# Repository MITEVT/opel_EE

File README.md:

# opel_EE

A collection of repositories relating to our Electric Opel GT Project

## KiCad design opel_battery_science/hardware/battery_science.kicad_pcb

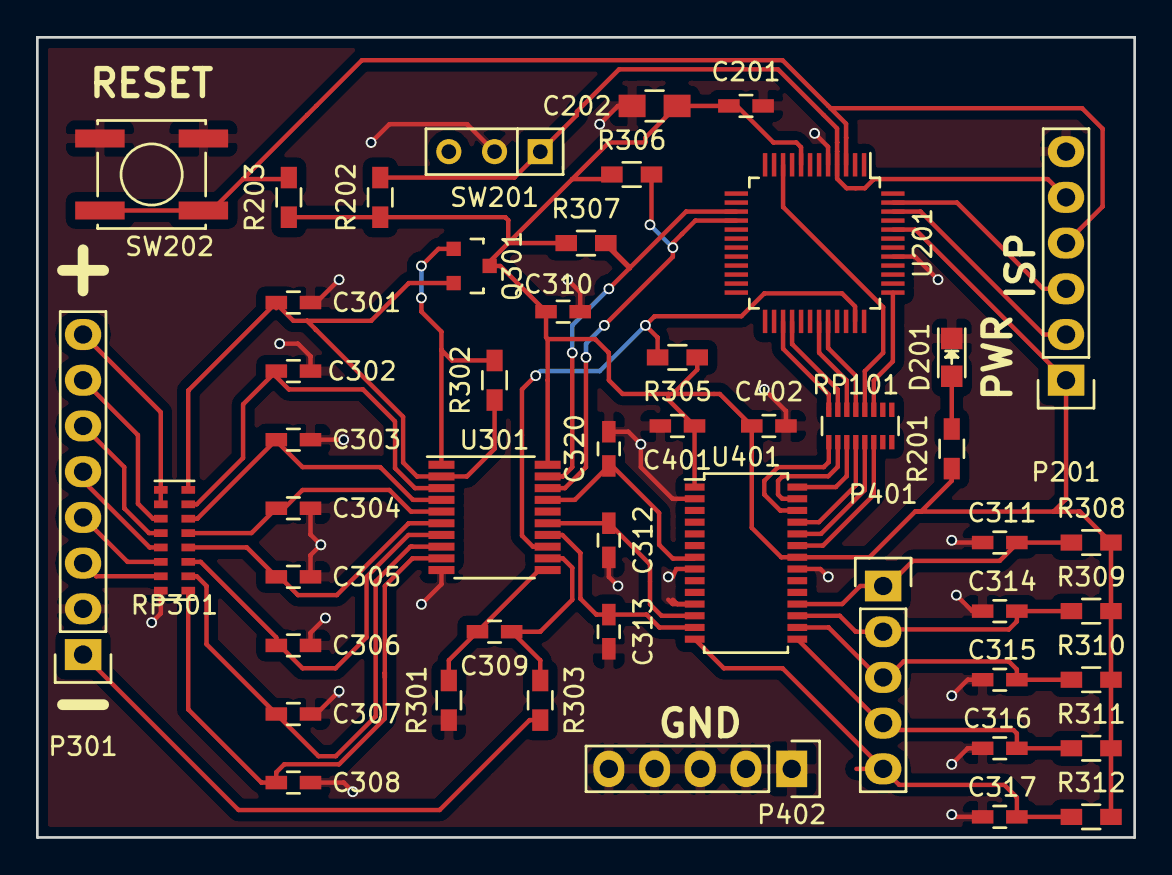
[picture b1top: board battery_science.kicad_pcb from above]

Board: 2 copper layers, 61.0 x 44.5 mm, 49 parts (0 on the bottom side), 48 nets.

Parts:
C201, C309, C311, C312, C314, C315, C316, C317: .1μF; C_0603_HandSoldering
C202: 1μF; C_0805_HandSoldering
C301: 10μF; C_0603_HandSoldering
C302, C303, C304, C305, C306, C307, C308, C320: 1μF; C_0603_HandSoldering
C310: 4.7μF; C_0603_HandSoldering
C313: 1nF; C_0603_HandSoldering
C401, C402: 100nF; C_0603_HandSoldering
D201: LED; LED_0805
P201: CONN_01X06; Pin_Header_Straight_1x06
P301: CONN_01X08; Pin_Header_Straight_1x08
P401, P402: CONN_01X05; Pin_Header_Straight_1x05
Q301: BSS84; SOT-23
R201: 100; R_0603_HandSoldering
R202, R203, R308, R309, R310, R311, R312: 10k; R_0603_HandSoldering
R301, R303: 1k; R_0603_HandSoldering
R302: 200k; R_0603_HandSoldering
R305, R306, R307: 4.7k; R_0603_HandSoldering
RP101: 47Ω; R_Array_Convex_8x0602
RP301: CAY16-101J8LF; R_Cat16-8
SW201: SPST; SW_Micro_SPST
SW202: SPST; SW_SPST_EVPBF
U201: LPC11C14; LQFP-48_7x7mm_Pitch0.5mm
U301: BQ76925; TSSOP-20_4.4x6.5mm_Pitch0.65mm
U401: ADS1148IPWR; TSSOP-28_4.4x9.7mm_Pitch0.65mm

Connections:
+3V3: C201.1, C202.1, C310.1, C401.1, C402.1, P201.1, Q301.3, R201.1, R202.1, R203.1, R305.1, R306.1, R307.1, R308.2, R309.2, R310.2, R311.2, R312.2, U201.8, U201.44, U301.20, U401.1, U401.22
/ADC/Thermistors/CS: RP101.5, U401.24
/ADC/Thermistors/DIN: RP101.2, U401.27
/ADC/Thermistors/DOUT: RP101.1, U401.26
/ADC/Thermistors/DRDY: RP101.4, U401.25
/ADC/Thermistors/SCLK: RP101.3, U401.28
/ADC/Thermistors/START: RP101.6, U401.23
/ADC/Thermistors/TH1: C311.1, P401.1, R308.1, U401.18
/ADC/Thermistors/TH2: C314.1, P401.2, R309.1, U401.17
/ADC/Thermistors/TH3: C315.1, P401.3, R310.1, U401.16
/ADC/Thermistors/TH4: C316.1, P401.4, R311.1, U401.15
/ADC/Thermistors/TH5: C317.1, P401.5, R312.1, U401.14
/ADC/Thermistors/VCOUT: C312.1, U301.15, U401.12
/ADC/Thermistors/VIOUT: C313.1, U301.14, U401.13
/ADC/Thermistors/VREF: C320.1, U301.17, U401.7
/BatteryMonitoring/ALERT: R305.2, U201.35, U301.13
/BatteryMonitoring/SCL: R307.2, U201.15, U301.19
/BatteryMonitoring/SDA: R306.2, U201.16, U301.18
/microcontroller/DRDY: RP101.13, U201.32
/microcontroller/MISO: RP101.16, U201.27
/microcontroller/MOSI: RP101.15, U201.28
/microcontroller/PROGRAM: P201.5, R202.2, SW201.1, U201.4
/microcontroller/RESET: P201.4, R203.2, SW202.1, U201.3
/microcontroller/RXD: P201.2, U201.46
/microcontroller/SCK: RP101.14, U201.31
/microcontroller/SSEL: RP101.12, U201.10
/microcontroller/START: RP101.11, U201.37
/microcontroller/TXD: P201.3, U201.47
GND: C201.2, C202.2, C301.2, C302.2, C303.2, C304.2, C305.2, C306.2, C307.2, C308.2, C310.2, C311.2, C312.2, C313.2, C314.2, C315.2, C316.2, C317.2, C320.2, C401.2, C402.2, D201.1, P201.6, P301.2, P402.1, P402.2, P402.3, P402.4, P402.5, R301.2, RP301.8, SW201.2, SW202.2, U201.5, U201.41, U301.10, U401.2, U401.8, U401.11, U401.21
unnamed: C301.1, Q301.2, R302.1, RP301.16, U301.2
unnamed: C302.1, RP301.15, U301.3
unnamed: C303.1, RP301.14, U301.4
unnamed: C304.1, RP301.13, U301.5
unnamed: C305.1, RP301.12, U301.6
unnamed: C306.1, RP301.11, U301.7
unnamed: C307.1, RP301.10, U301.8
unnamed: C308.1, RP301.9, U301.9
unnamed: C309.1, R303.1, U301.12
unnamed: C309.2, R301.1, U301.11
unnamed: D201.2, R201.2
unnamed: P301.1, R303.2
unnamed: P301.3, RP301.7
unnamed: P301.4, RP301.6
unnamed: P301.5, RP301.5
unnamed: P301.6, RP301.4
unnamed: P301.7, RP301.3
unnamed: P301.8, RP301.1, RP301.2
unnamed: Q301.1, R302.2, U301.1

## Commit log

2015-09-19 Initial Repo Setup
2015-09-19 Added KICAD libraries
2015-10-03 tete
2015-10-03 blah
2015-10-03 asldjf
2015-10-03 The log for the MiniMon
2015-10-03 Minimon screenshot
2015-10-10 finish
2015-10-10 Added dev board sub module
2015-10-10 fixing repo
2015-10-10 more fixing
2015-10-10 adding spec
2015-10-10 Updated spec
2015-10-10 Removed bullshit"
2015-10-10 This is a commit I'm doing
    This is a more detailed explanation of the the commit because hell yeah
2015-10-10 adding initial python validator
2015-10-10 updated can spec
2015-10-11 finished spec validator and format
2015-10-12 progress on log analysis
2015-10-12 removing swp files
2015-10-13 finish validator
2015-10-13 remove debug print
2015-10-14 fix bug involving error reporting and boundary checking
2015-10-16 cleanup of repo
2015-10-16 complete dev board schematic and layout
2015-10-17 remove can_validator from here.
2015-10-17 add can_validator submodule
2015-10-17 remove can_validator again
2015-10-24 Fixed many example errors
2015-10-24 Created template and added unionized data structure in CAN message object
2015-10-30 Added unit tests to tempalte and resolved soem compiler warnings
2015-11-14 Added PDM
2015-11-14 added opel fusebox
2015-11-21 Finished final template outeline
2015-11-21 Added 12V
2016-01-09 Velocity sensor circuit added
2016-01-16 hardware: initial commit
2016-04-02 relay box schematics first commit
2016-04-09 relay box updates
2016-04-09 updates to relay box schematics
2016-04-23 relay schematic updates and relay library
2016-04-30 updated relay box schematics, added VCF4-1000 footprint
2016-06-17 Created fake DI
2016-07-01 TestDI added UART printing
2016-07-12 Some changes, commiting before I mess with computer
2016-07-28 Added battery science code
2016-07-29 Fixed negative numbers
2016-07-29 Fixed errors and warnings
2016-07-31 Added new features, never had a successful test of measuring voltages with resistors
2016-08-05 Added PCB design
2016-08-08 Changes to offset and gain correction
2016-08-08 Fixed readings
2016-08-09 Added external ADC, fixed power
2016-08-09 Swapped out ADC part number
2016-08-15 Many fixes, corrected schematic, roughly tried to partition board
2016-08-16 Added ground connection for differnetial input
2016-08-16 Moved input pins for ease of programming and avoiding accidental negative readings
2016-09-17 Changes to power and connectors. Added LEDs
2016-09-17 Fixed LEDs
2016-09-24 shit
2016-09-24 remove from opel EE repo
2016-09-24 update gitmodules
2016-09-24 add submodule yeeeee
2016-10-08 Changed fake DI to submodule
2016-10-15 update lpc lib
2016-10-15 add ltc battery controller
2016-11-05 update opel repos
2017-01-11 add unity
2017-01-11 update submodules
2017-01-28 add psychic guacamole
